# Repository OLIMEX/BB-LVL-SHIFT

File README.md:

# BB-LVL-SHIFT
Breadboard friendly level shift module allow two boards with different voltages to talk with voltage levels from 1.65V to 5.5V

https://www.olimex.com/Products/Breadboarding/Components/BB-LVL-SHIFT/open-source-hardware

## Licensee
* Hardware is released under CERN Open Hardware Licence Version 2 - Strongly Reciprocal, all silkscreen credits to Bernardo Kastrup and Dean Belfield should remain;
* Software is released under MIT Licensee
* Documentation is released under CC BY-SA 3.0

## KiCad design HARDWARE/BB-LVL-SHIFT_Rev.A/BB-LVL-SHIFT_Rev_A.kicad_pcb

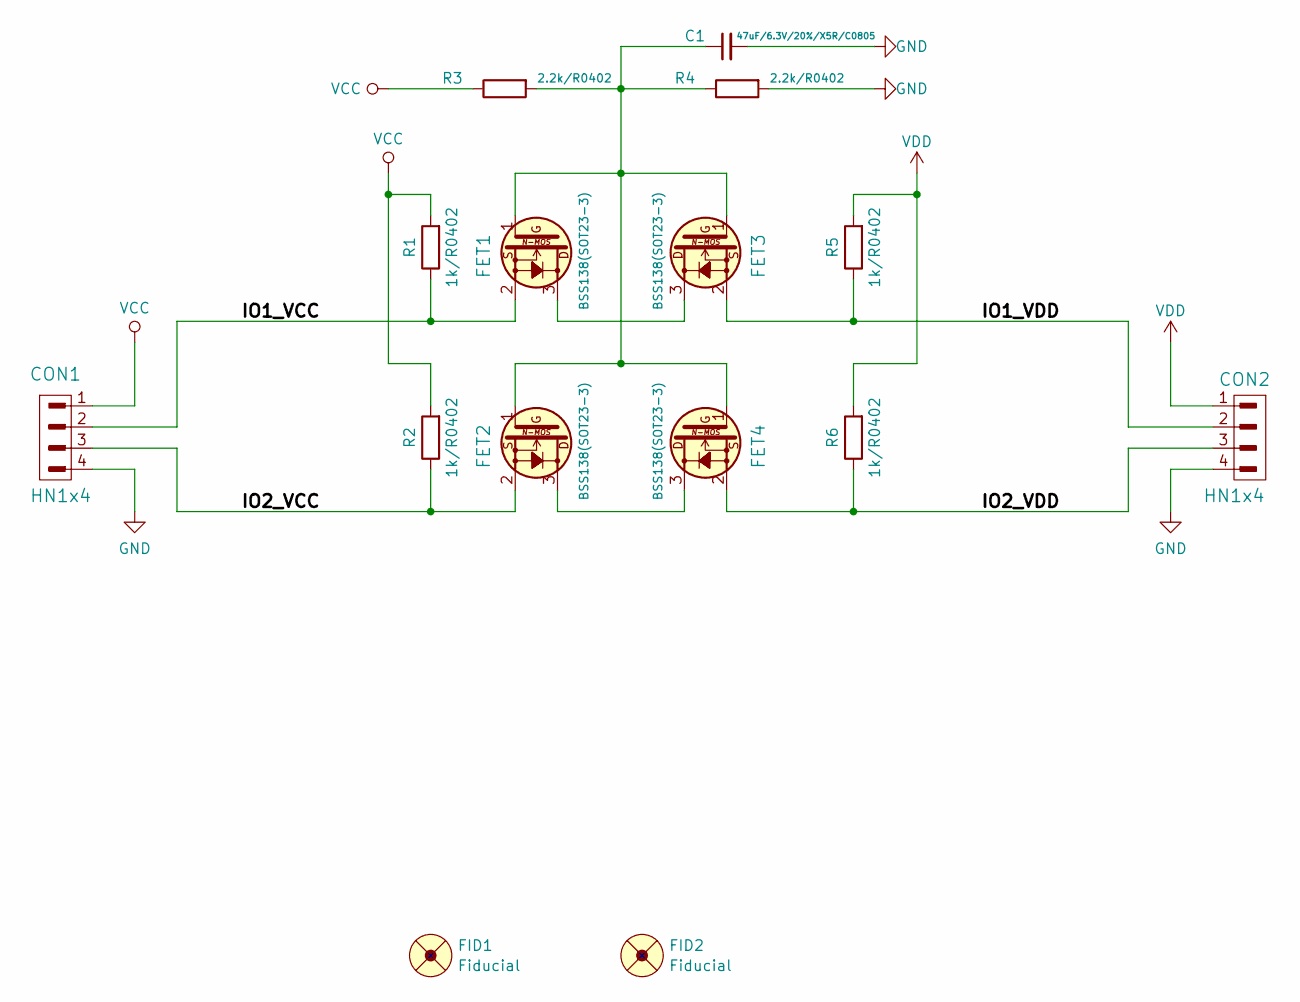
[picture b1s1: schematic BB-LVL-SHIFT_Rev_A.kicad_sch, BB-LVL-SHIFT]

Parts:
C1: 47uF/6.3V/20%/X5R/C0805; C_0805_5MIL_DWS
CON1, CON2: HN1x4
FET1, FET2, FET3, FET4: BSS138(SOT23-3); SOT23
FID1: Fiducial; Fiducial1x3
FID2: Fiducial; Fiducial1x3_Paste
R1, R2, R5, R6: 1k/R0402; R_0402_5MIL_DWS
R3, R4: 2.2k/R0402; R_0402_5MIL_DWS

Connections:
/IO1_VCC: CON1.2, FET1.2 (S), R1.1
/IO1_VDD: CON2.2, FET3.2 (S), R5.1
/IO2_VCC: CON1.3, FET2.2 (S), R2.1
/IO2_VDD: CON2.3, FET4.2 (S), R6.1
GND: C1.2, CON1.4, CON2.4, R4.2
unnamed: FET1.3 (D), FET3.3 (D)
unnamed: C1.1, FET1.1 (G), FET2.1 (G), FET3.1 (G), FET4.1 (G), R3.2, R4.1
unnamed: FET2.3 (D), FET4.3 (D)
VCC: CON1.1, R1.2, R2.2, R3.1
VDD: CON2.1, R5.2, R6.2

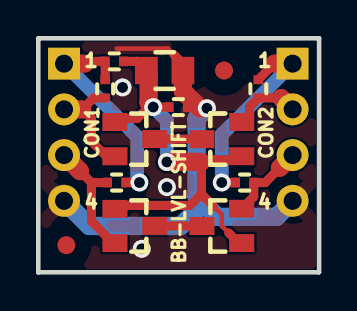
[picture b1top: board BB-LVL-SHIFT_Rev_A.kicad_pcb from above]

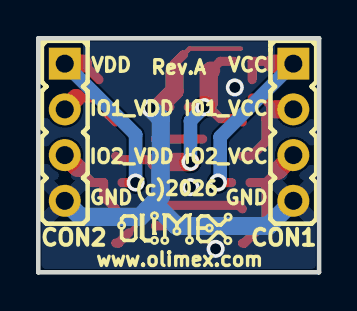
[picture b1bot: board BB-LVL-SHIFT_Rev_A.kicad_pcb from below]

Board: 2 copper layers, 15.6 x 13.0 mm, 16 parts (3 on the bottom side), 10 nets.

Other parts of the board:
Logo_OLIMEX_SMALL_TB: Logo_OLIMEX_SMALL_TB

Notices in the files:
HARDWARE/BB-LVL-SHIFT_Rev.A/BB-LVL-SHIFT_Rev_A.kicad_pcb:
(c)2026
